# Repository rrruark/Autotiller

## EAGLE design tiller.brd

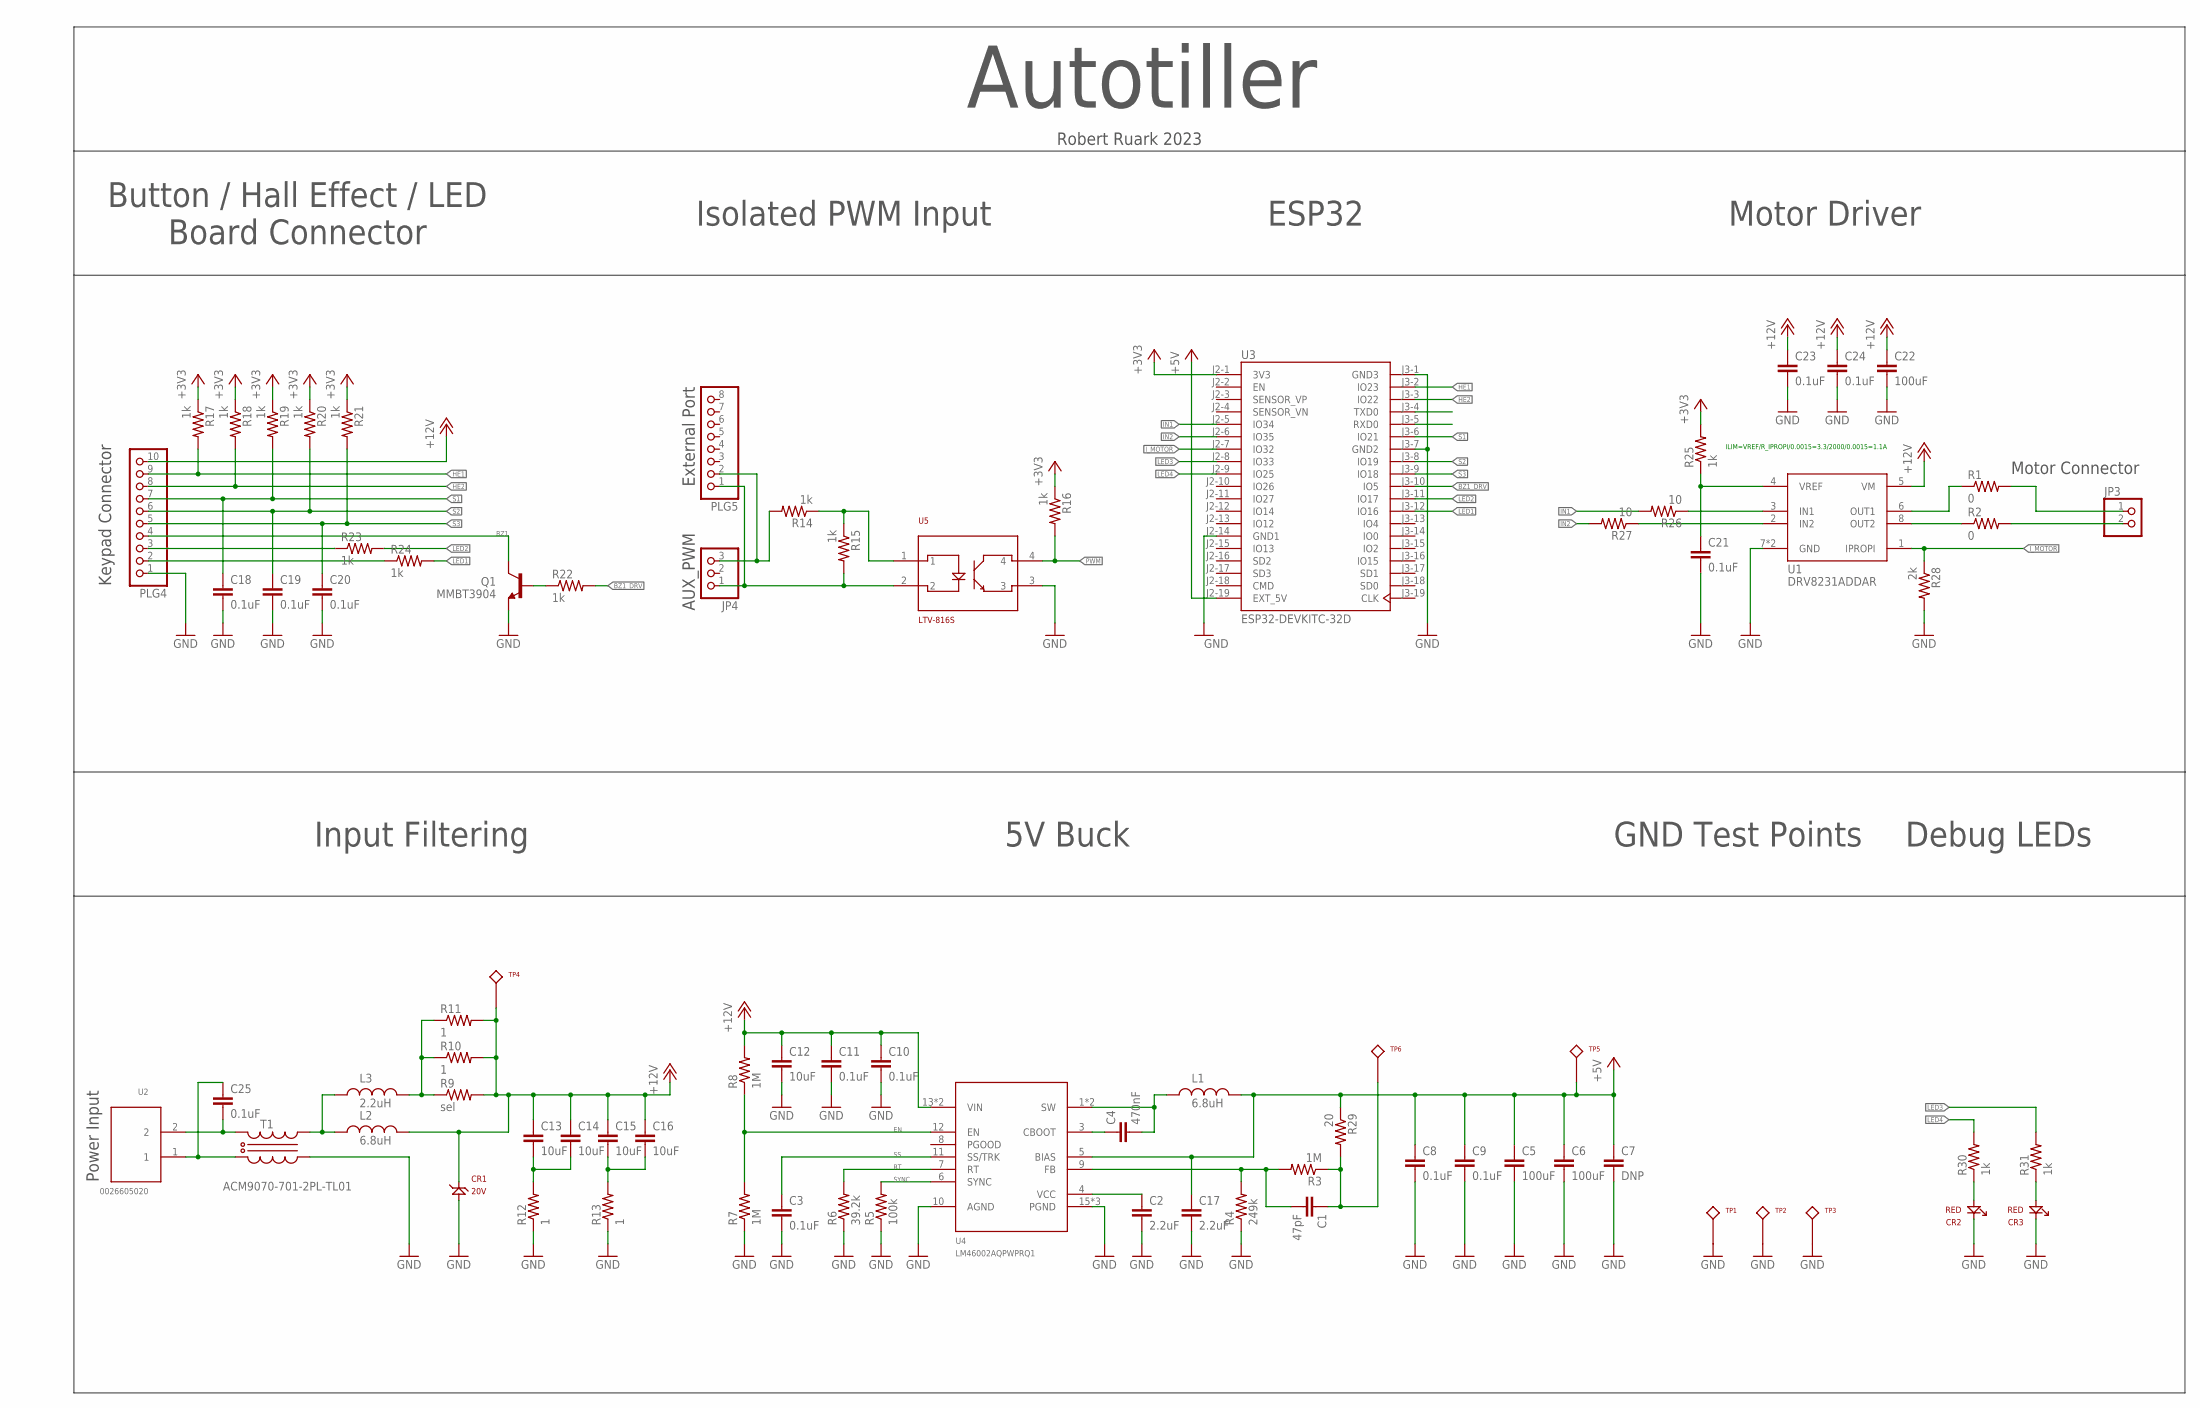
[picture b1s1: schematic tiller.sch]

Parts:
C1: 47pF; 0603
C2, C17: 2.2uF; 0805
C3, C8, C9, C10, C11, C18, C19, C20, C21, C23, C24, C25: 0.1uF; 0603
C4: 470nF; 0805
C5, C6, C22: 100uF; 1210
C7: DNP; 1210
C12, C13, C14, C15, C16: 10uF; 1210
CR1: 20V; DO-214AC
CR2, CR3: RED; 0603_DIODE
JP3: PINHD-1X2/90; 1X02/90
JP4: PINHD-1X3; 1X03
L1, L2: 6.8uH; NR6028
L3: 2.2uH; NR6028
PLG4: PINHD-1X10; 1X10
PLG5: PINHD-1X8; 1X08
Q1: MMBT3904; SOT23-3_CENTERED
R1, R2: 0; 1206
R3, R7, R8: 1M; 0603
R4: 249k; 0603
R5: 100k; 0603
R6: 39.2k; 0603
R9: sel; 1206
R10, R11, R12, R13: 1; 1206
R14, R15, R16, R17, R18, R19, R20, R21, R22, R23, R24, R25, R30, R31: 1k; 0603
R26, R27: 10; 0603
R28: 2k; 0603
R29: 20; 0603
T1: ACM9070-701-2PL-TL01; ACM9070
TP1, TP2, TP3: 5011; 5010
TP4, TP5, TP6: 5010
U1: DRV8231ADDAR; SOIC8_TP
U2: 0026605020; 3.96MM
U3: ESP32-DEVKITC-32D; MODULE_ESP32-DEVKITC-32D
U4: LM46002AQPWPRQ1; TSSOP16-POWER
U5: LTV-816S

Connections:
+3V3: R16.1, R17.1, R18.1, R19.1, R20.1, R21.1, R25.2, U3.J2-1 (3V3)
+5V: C5.1, C6.1, C7.1, C8.1, C9.1, C17.1, L1.P$2, R29.1, TP5.P$1, U3.J2-19 (EXT_5V), U4.5 (BIAS)
+12V: C10.1, C11.1, C12.1, C13.1, C14.1, C15.1, C16.1, C22.1, C23.1, C24.1, CR1.C (K), L2.P$2, PLG4.10, R8.2, R9.2, R10.2, R11.2, TP4.P$1, U1.5 (VM), U4.13 (VIN), U4.14 (VIN)
BST: C4.1, U4.3 (CBOOT)
BZ1: PLG4.4, Q1.3 (C)
BZ1_DRV: R22.2, U3.J3-10 (IO5)
EN: R7.2, R8.1, U4.12 (EN)
GND: C2.2, C3.2, C5.2, C6.2, C7.2, C8.2, C9.2, C10.2, C11.2, C12.2, C17.2, C18.2, C19.2, C20.2, C21.2, C22.2, C23.2, C24.2, CR1.A, CR2.K, CR3.K, PLG4.1, Q1.2 (E), R4.1, R5.1, R6.1, R7.1, R12.1, R13.1, R28.2, T1.1OUT, TP1.P$1, TP2.P$1, TP3.P$1, U1.7 (GND), U1.TP (GND), U3.J2-14 (GND1), U3.J3-1 (GND3), U3.J3-7 (GND2), U4.10 (AGND), U4.15 (PGND), U4.16 (PGND), U4.P$1 (PGND), U5.3
HE1: PLG4.9, R17.2, U3.J3-2 (IO23)
HE2: PLG4.8, R18.2, U3.J3-3 (IO22)
IN1: R26.2, U3.J2-5 (IO34)
IN2: R27.2, U3.J2-6 (IO35)
I_MOTOR: R28.1, U1.1 (IPROPI), U3.J2-7 (IO32)
LED1: R24.2, U3.J3-12 (IO16)
LED2: R23.2, U3.J3-11 (IO17)
LED3: R31.2, U3.J2-8 (IO33)
LED4: R30.2, U3.J2-9 (IO25)
MOTOR_1: JP3.1, R1.2
MOTOR_2: JP3.2, R2.2
unnamed: C25.1, T1.1IN, U2.1
unnamed: C2.1, U4.4 (VCC)
unnamed: R1.1, U1.6 (OUT1)
unnamed: R2.1, U1.8 (OUT2)
unnamed: C1.1, R3.1, R29.2, TP6.P$1
unnamed: CR2.A, R30.1
unnamed: R14.1, R15.1, U5.1
unnamed: C1.2, R3.2, R4.2, U4.9 (FB)
unnamed: PLG4.3, R23.1
unnamed: Q1.1 (B), R22.1
unnamed: C25.2, T1.2IN, U2.2
unnamed: CR3.A, R31.1
unnamed: L3.P$2, R9.1, R10.1, R11.1
unnamed: C13.2, C14.2, R12.2
unnamed: PLG4.2, R24.1
unnamed: C21.1, R25.1, U1.4 (VREF)
unnamed: C15.2, C16.2, R13.2
unnamed: R27.1, U1.2 (IN2)
unnamed: R26.1, U1.3 (IN1)
PWM: R16.2, U5.4
PWMIN: JP4.3, PLG5.2, R14.2
RT: R6.2, U4.7 (RT)
RTN: JP4.1, PLG5.1, R15.2, U5.2
S1: C18.1, PLG4.7, R19.2, U3.J3-6 (IO21)
S2: C19.1, PLG4.6, R20.2, U3.J3-8 (IO19)
S3: C20.1, PLG4.5, R21.2, U3.J3-9 (IO18)
SS: C3.1, U4.11 (SS/TRK)
SW: C4.2, L1.P$1, U4.1 (SW), U4.2 (SW)
SYNC: R5.2, U4.6 (SYNC)
VINF: L2.P$1, L3.P$1, T1.2OUT

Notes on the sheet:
ILIM=VREF/R_IPROPI/0.0015=3.3/2000/0.0015=1.1A
Motor Connector
Keypad Connector
External Port
AUX_PWM
Power Input
Input Filtering
5V Buck
GND Test Points
Debug LEDs
Motor Driver
ESP32
Isolated PWM Input
Button / Hall Effect / LED Board Connector
Autotiller
Robert Ruark 2023

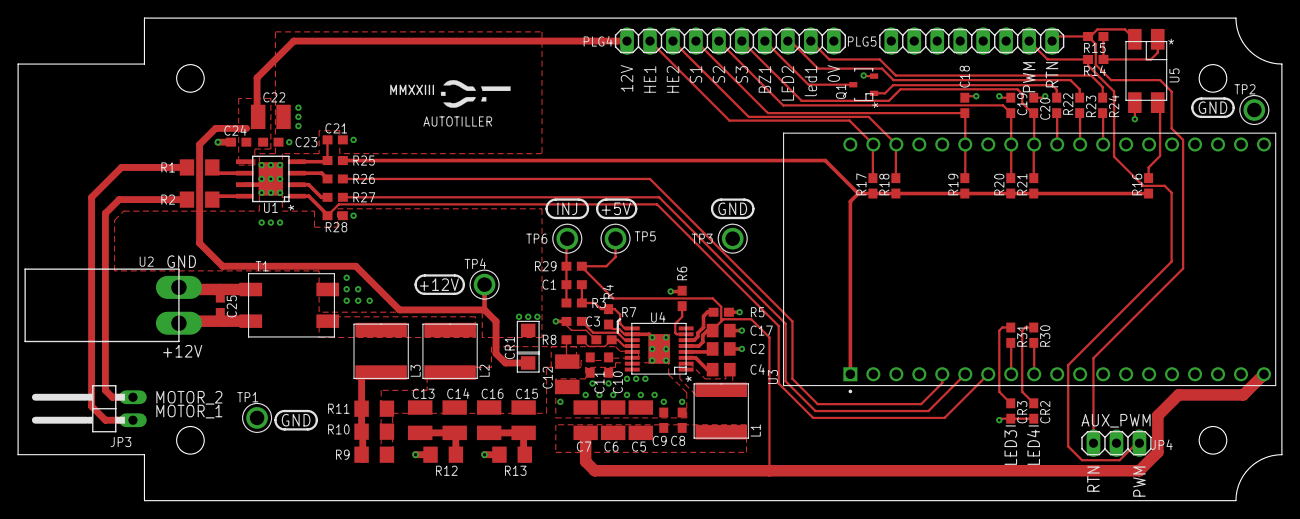
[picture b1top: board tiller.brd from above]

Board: 2 copper layers, 139.7 x 53.3 mm, 79 parts (0 on the bottom side), 49 nets.
